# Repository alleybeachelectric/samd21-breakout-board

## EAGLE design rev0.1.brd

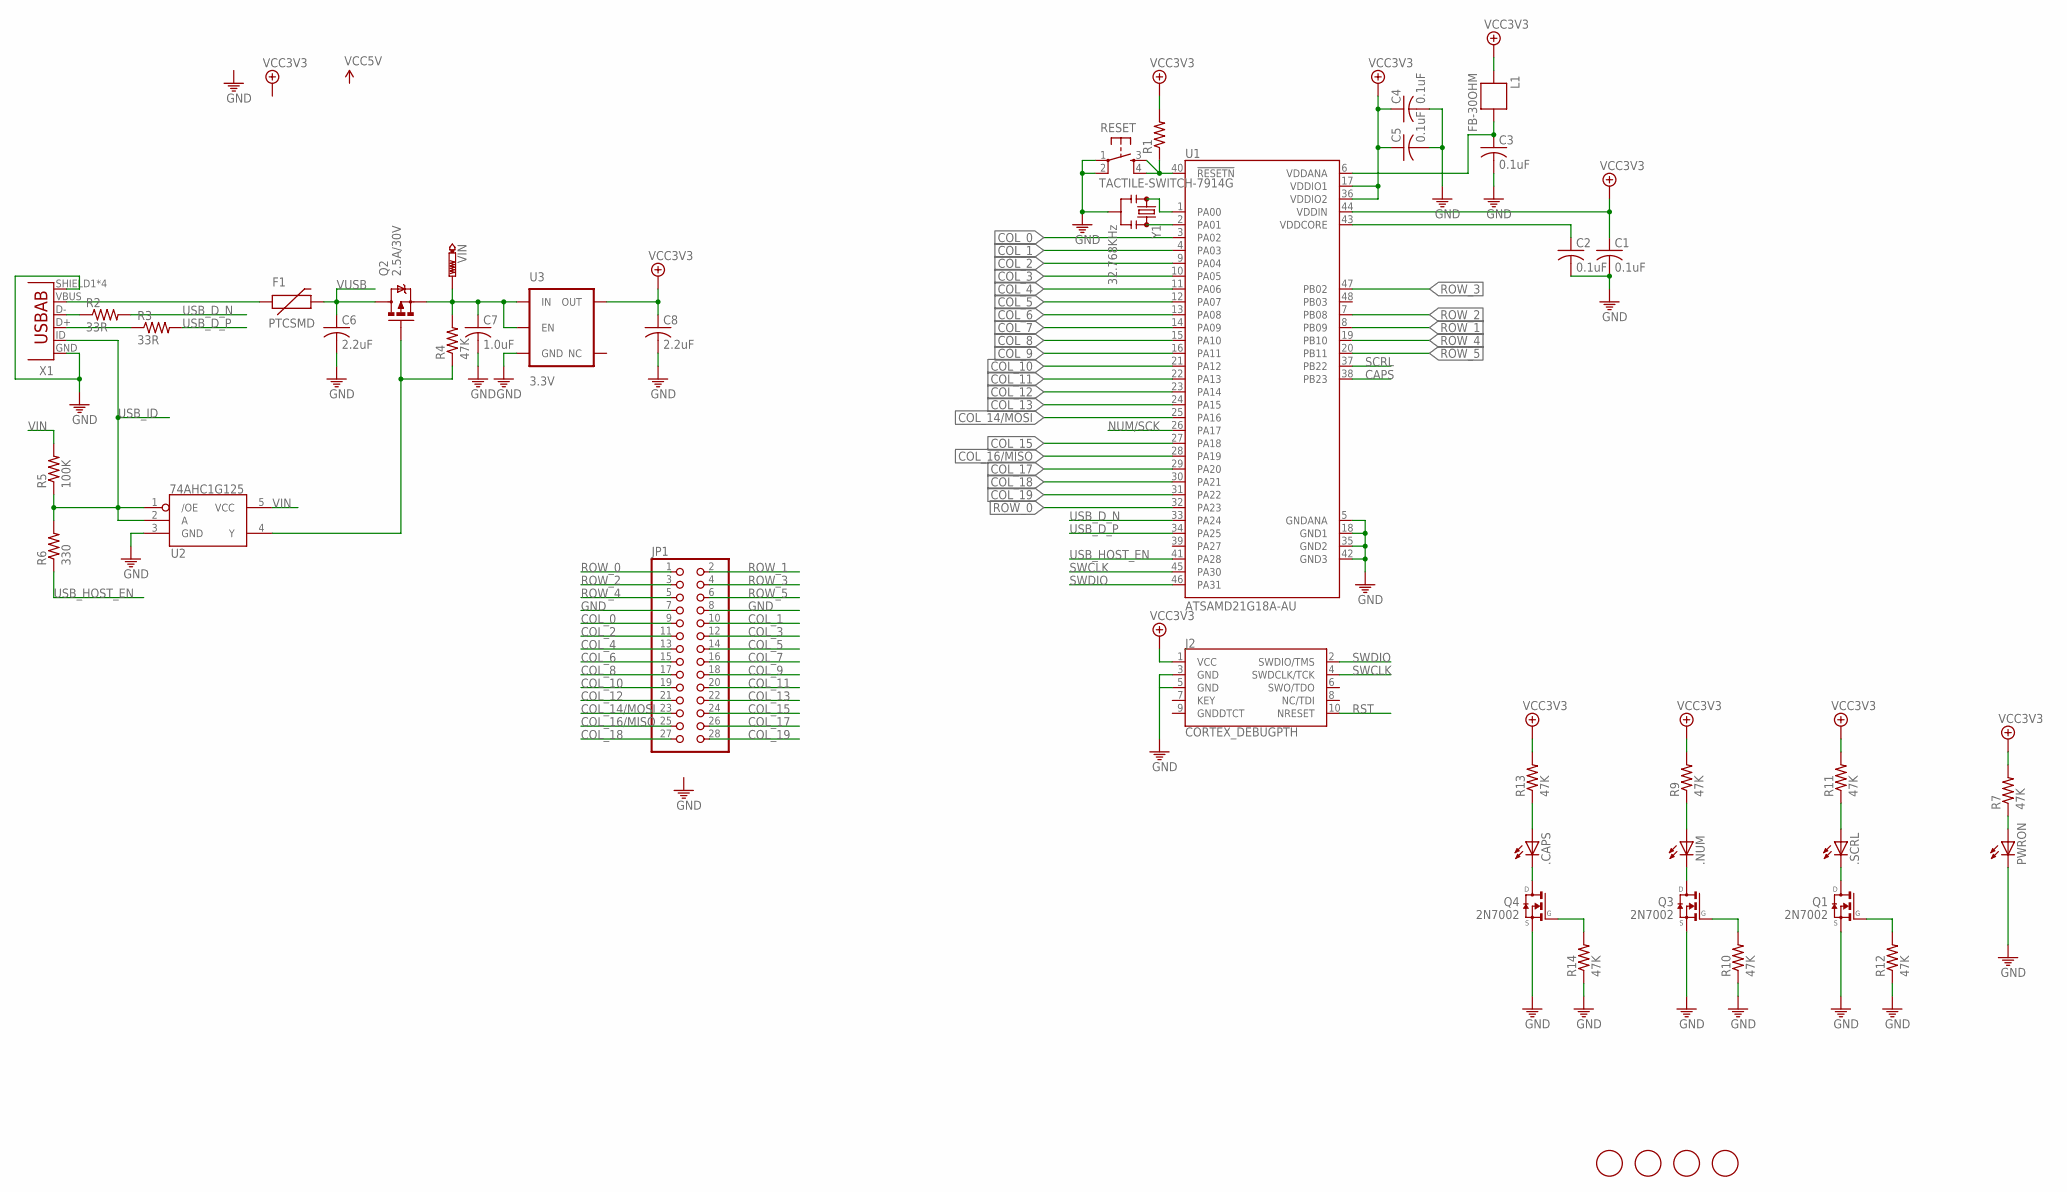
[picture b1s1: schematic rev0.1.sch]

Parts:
.CAPS, .NUM, .SCRL: LEDCHIPLED_1206; CHIPLED_1206
C1, C2, C3, C4, C5: 0.1uF; C0603
C6, C8: 2.2uF; C0603
C7: 1.0uF; C0603
F1: PTCSMD; PTC-1206
J2: CORTEX_DEBUGPTH; 2X5-PTH-1.27MM
JP1: PINHD-2X14-CB; 2X14-CLEANBIG
L1: FB-30OHM; 0603
PWRON: LEDCHIPLED_1206; CHIPLED_1206
Q1, Q3, Q4: 2N7002; SOT23
Q2: 2.5A/30V; SOT23-3
R1: R-US_R0603; R0603
R2, R3: 33R; R0603
R4, R7, R9, R10, R11, R12, R13, R14: 47K; R0603
R5: 100K; R0603
R6: 330; R0603
RESET: TACTILE-SWITCH-7914G; 7914G
U1: ATSAMD21G18A-AU; QFP50P900X900X120-48N
U2: 74AHC1G125; SOT23-5
U3: 3.3V; SOT23-5
U$6, U$19, U$20, U$21: FIDUCIAL; FIDUCIAL_1MM
VIN: PTR1PAD1-17; P1-17
X1: USB-AB"; USB_AB_MICRO_1:1_V2
Y1: 32.768KHz; RESONATOR-SMD

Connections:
CAPS: Q4.1 (G), R14.2, U1.38 (PB23)
COL_0: JP1.9, U1.3 (PA02)
COL_1: JP1.10, U1.4 (PA03)
COL_2: JP1.11, U1.9 (PA04)
COL_3: JP1.12, U1.10 (PA05)
COL_4: JP1.13, U1.11 (PA06)
COL_5: JP1.14, U1.12 (PA07)
COL_6: JP1.15, U1.13 (PA08)
COL_7: JP1.16, U1.14 (PA09)
COL_8: JP1.17, U1.15 (PA10)
COL_9: JP1.18, U1.16 (PA11)
COL_10: JP1.19, U1.21 (PA12)
COL_11: JP1.20, U1.22 (PA13)
COL_12: JP1.21, U1.23 (PA14)
COL_13: JP1.22, U1.24 (PA15)
COL_14/MOSI: JP1.23, U1.25 (PA16)
COL_15: JP1.24, U1.27 (PA18)
COL_16/MISO: JP1.25, U1.28 (PA19)
COL_17: JP1.26, U1.29 (PA20)
COL_18: JP1.27, U1.30 (PA21)
COL_19: JP1.28, U1.31 (PA22)
D_N: R2.1, X1.D-
D_P: R3.1, X1.D+
GND: C1.2, C2.2, C3.2, C4.2, C5.2, C6.2, C7.2, C8.2, J2.3 (GND), J2.5 (GND), JP1.7, JP1.8, PWRON.C, Q1.2 (S), Q3.2 (S), Q4.2 (S), R10.1, R12.1, R14.1, RESET.1, RESET.2, U1.5 (GNDANA), U1.18 (GND1), U1.35 (GND2), U1.42 (GND3), U2.3 (GND), U3.2 (GND), X1.GND, X1.SHIELD1 (SHIELD), X1.SHIELD2 (SHIELD), X1.SHIELD3 (SHIELD), X1.SHIELD4 (SHIELD), Y1.2
unnamed: U1.1 (PA00), Y1.1
unnamed: C2.1, U1.43 (VDDCORE)
unnamed: U1.2 (PA01), Y1.3
unnamed: C3.1, L1.1, U1.6 (VDDANA)
unnamed: Q2.1 (G), R4.1, U2.4 (Y)
unnamed: PWRON.A, R7.1
unnamed: .SCRL.A, R11.1
unnamed: .NUM.A, R9.1
unnamed: .NUM.C, Q3.3 (D)
unnamed: .SCRL.C, Q1.3 (D)
unnamed: .CAPS.A, R13.1
unnamed: .CAPS.C, Q4.3 (D)
NUM/SCK: Q3.1 (G), R10.2, U1.26 (PA17)
ROW_0: JP1.1, U1.32 (PA23)
ROW_1: JP1.2, U1.8 (PB09)
ROW_2: JP1.3, U1.7 (PB08)
ROW_3: JP1.4, U1.47 (PB02)
ROW_4: JP1.5, U1.19 (PB10)
ROW_5: JP1.6, U1.20 (PB11)
RST: J2.10 (NRESET), R1.1, RESET.3, RESET.4, U1.40 (!RESETN)
SCRL: Q1.1 (G), R12.2, U1.37 (PB22)
SWCLK: J2.4 (SWDCLK/TCK), U1.45 (PA30)
SWDIO: J2.2 (SWDIO/TMS), U1.46 (PA31)
USBVIN: F1.1, X1.VBUS
USB_D_N: R2.2, U1.33 (PA24)
USB_D_P: R3.2, U1.34 (PA25)
USB_HOST_EN: R6.1, U1.41 (PA28)
USB_ID: R5.1, R6.2, U2.1 (/OE), U2.2 (A), X1.ID (USBID)
VCC3V3: C1.1, C4.1, C5.1, C8.1, J2.1 (VCC), L1.2, R1.2, R7.2, R9.2, R11.2, R13.2, U1.17 (VDDIO1), U1.36 (VDDIO2), U1.44 (VDDIN), U3.5 (OUT)
VIN: C7.1, Q2.2 (S), R4.2, R5.2, U2.5 (VCC), U3.1 (IN), U3.3 (EN), VIN.TP
VUSB: C6.1, F1.2, Q2.3 (D)

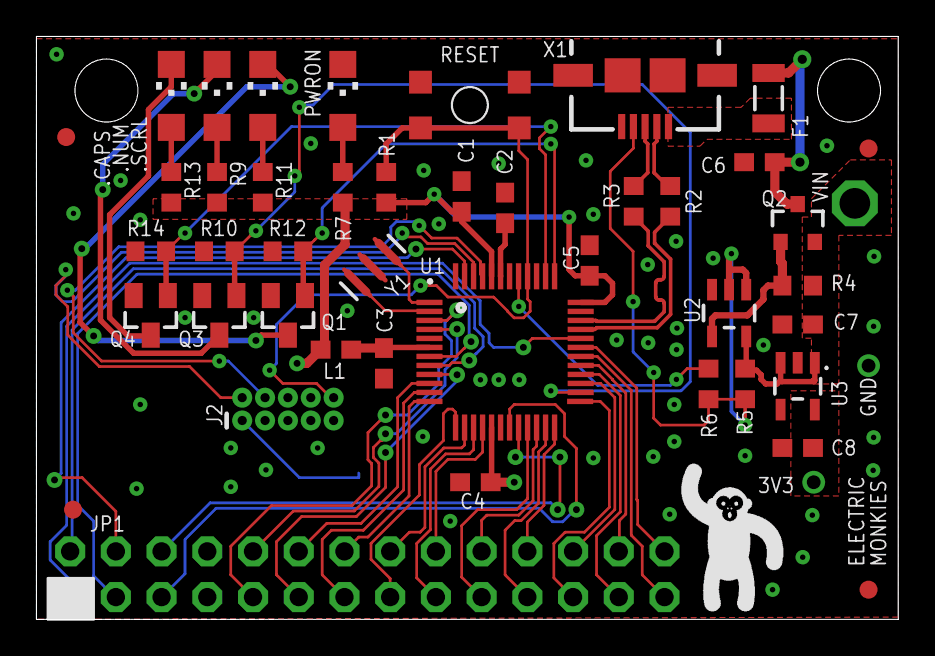
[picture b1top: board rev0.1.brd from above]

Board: 2 copper layers, 47.9 x 32.4 mm, 45 parts (0 on the bottom side), 55 nets.

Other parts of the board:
DRILEGEND: DRILEGEND

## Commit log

2017-03-28 initial commit.

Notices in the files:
parts and their libraries:
SparkFun-PowerIC: Licensing: Creative Commons ShareAlike 4.0 International - https://creativecommons.org/licenses/by-sa/4.0
